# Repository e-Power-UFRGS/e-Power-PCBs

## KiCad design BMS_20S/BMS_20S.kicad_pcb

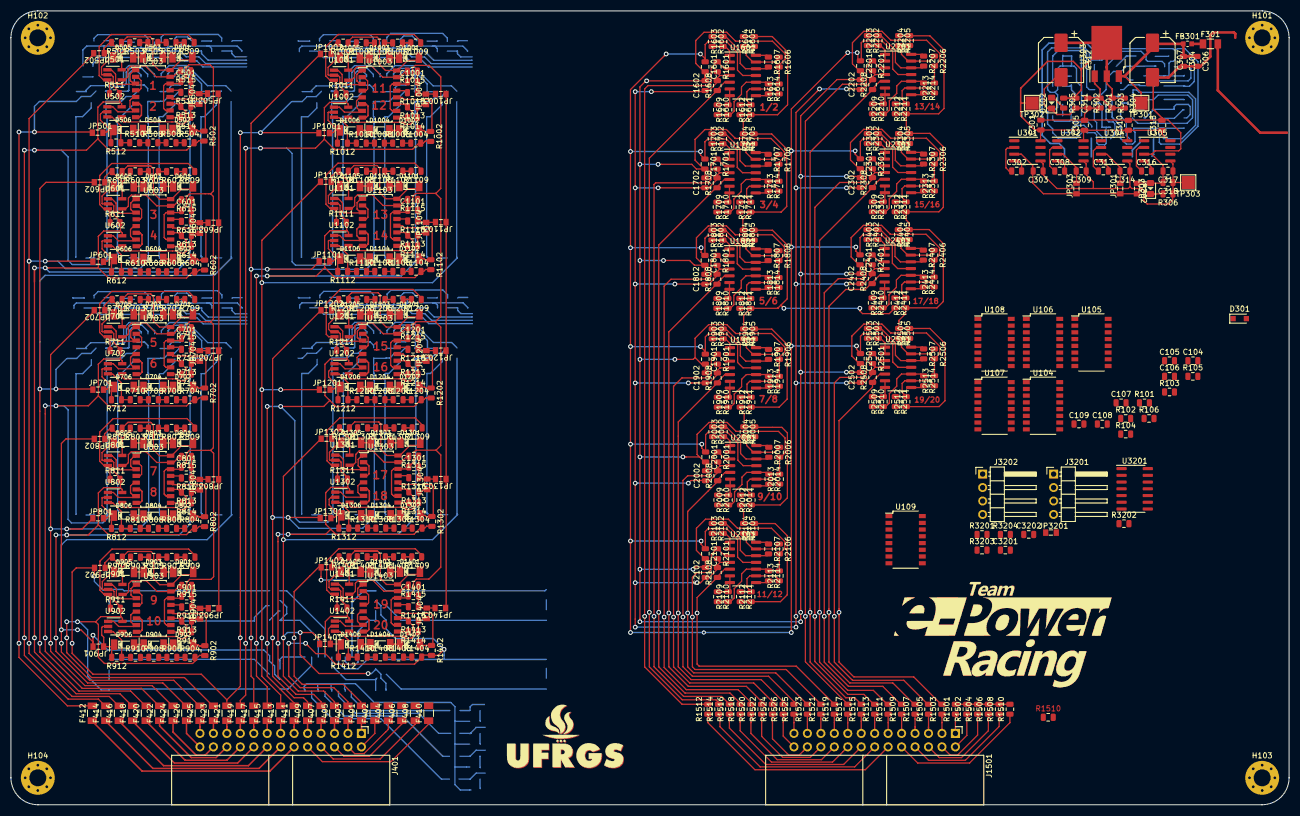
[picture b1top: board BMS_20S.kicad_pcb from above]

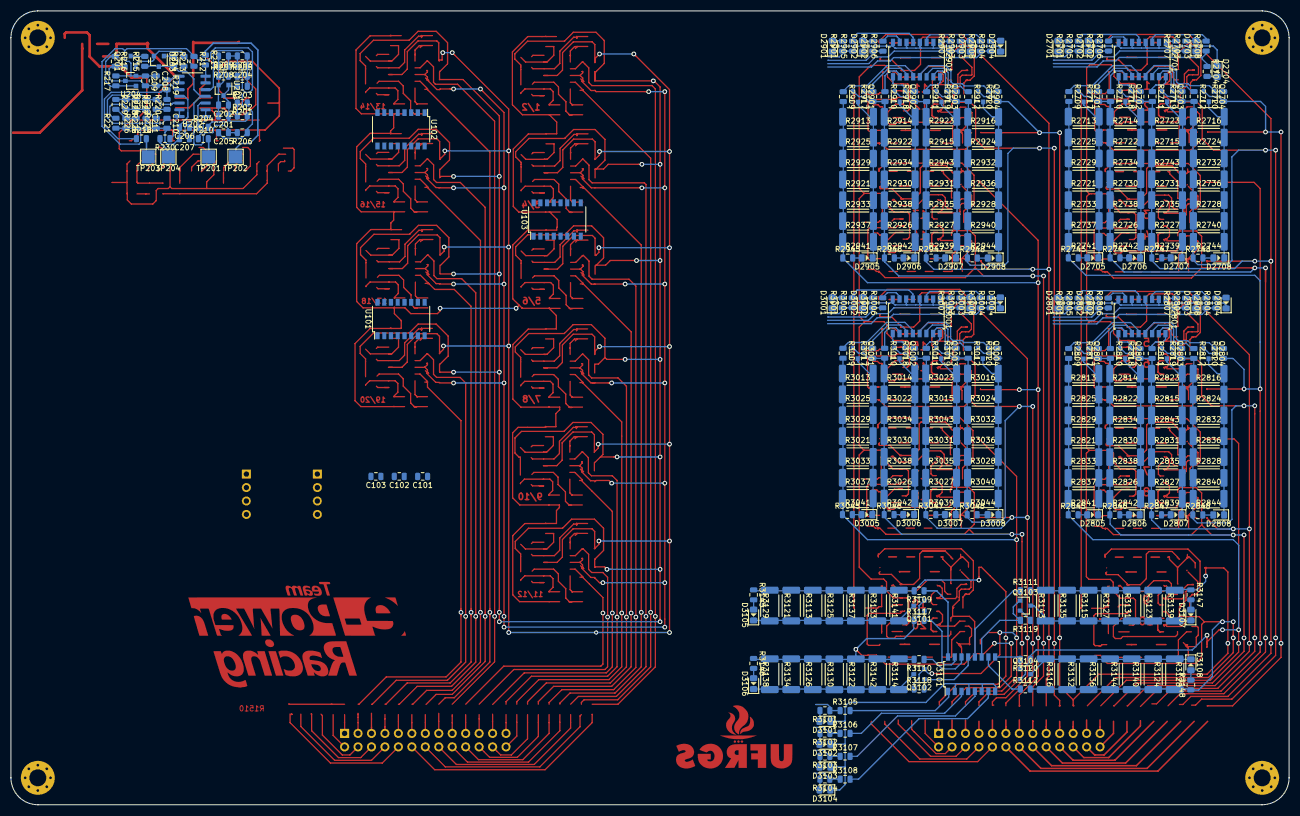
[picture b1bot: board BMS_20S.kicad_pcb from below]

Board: 4 copper layers, 241.3 x 149.9 mm, 958 parts (361 on the bottom side), 596 nets.

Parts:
C101, C102, C103, C104, C105, C106, C107, C108, C109, C202, C203, C205, C207, C209, C210, C301, C303, C304, C305, C309, C310, C311, C314, C315, C317, C501, C601, C701, C801, C901, C1001, C1101, C1201, C1301, C1401, C1601, C1602, C1701, C1702, C1801, C1802, C1901, C1902, C2001, C2002, C2101, C2102, C2201, C2202, C2301, C2302, C2401, C2402, C2501, C2502, C3201, C3202: 100nF; C_0805_2012Metric
C201, C204, C206, C208, C211, C302, C306, C308, C313, C316, C318: 10uF; C_0805_2012Metric
C307, C312: 470uF; CP_Elec_8x10
D301: 1N5819; D_SOD-323_HandSoldering
D302, D303, D2701, D2702, D2703, D2704, D2705, D2706, D2707, D2708, D2801, D2802, D2803, D2804, D2805, D2806, D2807, D2808, D2901, D2902, D2903, D2904, D2905, D2906, D2907, D2908, D3001, D3002, D3003, D3004, D3005, D3006, D3007, D3008, D3101, D3102, D3103, D3104, D3105, D3106, D3107, D3108: LED; LED_0805_1.15x1.40mm_HandSolder
D501, D502, D503, D504, D505, D506, D601, D602, D603, D604, D605, D606, D701, D702, D703, D704, D705, D706, D801, D802, D803, D804, D805, D806, D901, D902, D903, D904, D905, D906, D1001, D1002, D1003, D1004, D1005, D1006, D1101, D1102, D1103, D1104, D1105, D1106, D1201, D1202, D1203, D1204, D1205, D1206, D1301, D1302, D1303, D1304, D1305, D1306, D1401, D1402, D1403, D1404, D1405, D1406: LL4148; SOD-80
F301: Fuse_1206; FUSE_1206_3216Metric
F401, F402, F403, F404, F405, F406, F407, F408, F409, F410, F411, F412, F413, F414, F415, F416, F417, F418, F419, F420, F421, F422, F423, F424, F425, F426: Fuse; FUSE_1206_3216Metric
FB301: Ferrite_Bead; FB_0603_1608Metric
H101, H102, H103, H104: MountingHole_Pad; MountingHole_3.2mm_M3_Pad_Via
J401: VOLT_IDC_26_CONN; IDC-Header_2x13_P2.54mm_Horizontal
J1501: TEMP_IDC_26_CONN; IDC-Header_2x13_P2.54mm_Horizontal
J3201: Current_Conn; PinHeader_1x04_P2.54mm_Horizontal
J3202: BSPD_Conn; PinHeader_1x04_P2.54mm_Horizontal
JP301, JP302, JP303, JP501, JP502, JP503, JP504, JP601, JP602, JP603, JP604, JP701, JP702, JP703, JP704, JP801, JP802, JP803, JP804, JP901, JP902, JP903, JP904, JP1001, JP1002, JP1003, JP1004, JP1101, JP1102, JP1103, JP1104, JP1201, JP1202, JP1203, JP1204, JP1301, JP1302, JP1303, JP1304, JP1401, JP1402, JP1403, JP1404: 0R; zero_ohm_resistor_0805
JP3201: jumper; zero_ohm_resistor_0805
Q201: BC558; SOT-23
Q2701, Q2702, Q2703, Q2704, Q2801, Q2802, Q2803, Q2804, Q2901, Q2902, Q2903, Q2904, Q3001, Q3002, Q3003, Q3004, Q3101, Q3102, Q3103, Q3104: Si2302DS; SOT-23
R101, R102, R103, R104, R105, R106, R203, R204, R205, R207, R208, R209, R212, R213, R214, R215, R216, R217, R222, R223, R225, R228, R301, R501, R502, R503, R504, R505, R506, R507, R508, R509, R510, R511, R512, R513, R514, R515, R516, R601, R602, R603, R604, R605, R606, R607, R608, R609, R610, R611, R612, R613, R614, R615, R616, R701, R702, R703, R704, R705, R706, R707, R708, R709, R710, R711, R712, R713, R714, R715, R716, R801, R802, R803, R804, R805, R806, R807, R808, R809, R810, R811, R812, R813, R814, R815, R816, R901, R902, R903, R904, R905, R906, R907, R908, R909, R910, R911, R912, R913, R914, R915, R916, R1001, R1002, R1003, R1004, R1005, R1006, R1007, R1008, R1009, R1010, R1011, R1012, R1013, R1014, R1015, R1016, R1101, R1102, R1103, R1104, R1105, R1106, R1107, R1108, R1109, R1110, R1111, R1112, R1113, R1114, R1115, R1116, R1201, R1202, R1203, R1204, R1205, R1206, R1207, R1208, R1209, R1210, R1211, R1212, R1213, R1214, R1215, R1216, R1301, R1302, R1303, R1304, R1305, R1306, R1307, R1308, R1309, R1310, R1311, R1312, R1313, R1314, R1315, R1316, R1401, R1402, R1403, R1404, R1405, R1406, R1407, R1408, R1409, R1410, R1411, R1412, R1413, R1414, R1415, R1416, R1601, R1608, R1701, R1708, R1801, R1808, R1901, R1908, R2001, R2008, R2101, R2108, R2201, R2208, R2301, R2308, R2401, R2408, R2501, R2508, R2709, R2710, R2711, R2712, R2809, R2810, R2811, R2812, R2909, R2910, R2911, R2912, R3009, R3010, R3011, R3012, R3109, R3110, R3111, R3112: 1K; R_0805_2012Metric
R201, R202: 100R; R_0805_2012Metric
R206, R220, R1602, R1603, R1604, R1605, R1606, R1607, R1609, R1610, R1611, R1612, R1613, R1614, R1702, R1703, R1704, R1705, R1706, R1707, R1709, R1710, R1711, R1712, R1713, R1714, R1802, R1803, R1804, R1805, R1806, R1807, R1809, R1810, R1811, R1812, R1813, R1814, R1902, R1903, R1904, R1905, R1906, R1907, R1909, R1910, R1911, R1912, R1913, R1914, R2002, R2003, R2004, R2005, R2006, R2007, R2009, R2010, R2011, R2012, R2013, R2014, R2102, R2103, R2104, R2105, R2106, R2107, R2109, R2110, R2111, R2112, R2113, R2114, R2202, R2203, R2204, R2205, R2206, R2207, R2209, R2210, R2211, R2212, R2213, R2214, R2302, R2303, R2304, R2305, R2306, R2307, R2309, R2310, R2311, R2312, R2313, R2314, R2402, R2403, R2404, R2405, R2406, R2407, R2409, R2410, R2411, R2412, R2413, R2414, R2502, R2503, R2504, R2505, R2506, R2507, R2509, R2510, R2511, R2512, R2513, R2514, R2717, R2718, R2719, R2720, R2817, R2818, R2819, R2820, R2917, R2918, R2919, R2920, R3017, R3018, R3019, R3020, R3117, R3118, R3119, R3120, R3201, R3202, R3203, R3204: 10K; R_0805_2012Metric
R210, R211, R218, R219, R224, R229, R230, R1501, R1502, R1503, R1504, R1505, R1506, R1507, R1508, R1509, R1510, R1510#2, R1511, R1512, R1513, R1514, R1515, R1516, R1517, R1518, R1519, R1520, R1521, R1522, R1523, R1524, R1525, R1526: 0R; R_0805_2012Metric
R221, R226, R227: 100K; R_0805_2012Metric
R302, R304: ADJ; R_0805_2012Metric
R303, R305, R306, R2701, R2702, R2703, R2704, R2705, R2706, R2707, R2708, R2745, R2746, R2747, R2748, R2801, R2802, R2803, R2804, R2805, R2806, R2807, R2808, R2845, R2846, R2847, R2848, R2901, R2902, R2903, R2904, R2905, R2906, R2907, R2908, R2945, R2946, R2947, R2948, R3001, R3002, R3003, R3004, R3005, R3006, R3007, R3008, R3045, R3046, R3047, R3048, R3101, R3102, R3103, R3104, R3105, R3106, R3107, R3108, R3145, R3146, R3147, R3148: 330R; R_0805_2012Metric
R2713, R2714, R2715, R2716, R2721, R2722, R2723, R2724, R2725, R2726, R2727, R2728, R2729, R2730, R2731, R2732, R2733, R2734, R2735, R2736, R2737, R2738, R2739, R2740, R2741, R2742, R2743, R2744, R2813, R2814, R2815, R2816, R2821, R2822, R2823, R2824, R2825, R2826, R2827, R2828, R2829, R2830, R2831, R2832, R2833, R2834, R2835, R2836, R2837, R2838, R2839, R2840, R2841, R2842, R2843, R2844, R2913, R2914, R2915, R2916, R2921, R2922, R2923, R2924, R2925, R2926, R2927, R2928, R2929, R2930, R2931, R2932, R2933, R2934, R2935, R2936, R2937, R2938, R2939, R2940, R2941, R2942, R2943, R2944, R3013, R3014, R3015, R3016, R3021, R3022, R3023, R3024, R3025, R3026, R3027, R3028, R3029, R3030, R3031, R3032, R3033, R3034, R3035, R3036, R3037, R3038, R3039, R3040, R3041, R3042, R3043, R3044, R3113, R3114, R3115, R3116, R3121, R3122, R3123, R3124, R3125, R3126, R3127, R3128, R3129, R3130, R3131, R3132, R3133, R3134, R3135, R3136, R3137, R3138, R3139, R3140, R3141, R3142, R3143, R3144: 100R; R_2512_6332Metric
TP201: 2.2727V_TP; TestPoint_Pad_2.5x2.5mm
TP202: 1.8V_TP; TestPoint_Pad_2.5x2.5mm
TP203: 5.000V_TP; TestPoint_Pad_2.5x2.5mm
TP204: 0.850V_TP; TestPoint_Pad_2.5x2.5mm
TP301: 12V_TP; TestPoint_Pad_2.5x2.5mm
TP302: 5V_TP; TestPoint_Pad_2.5x2.5mm
TP303: -5V_TP; TestPoint_Pad_2.5x2.5mm
U101, U102, U103, U104, U105, U106: 74HC4051; SOP-16_4.4x10.4mm_P1.27mm
U107, U108, U109: 74HC595; SOP-16_4.4x10.4mm_P1.27mm
U201, U203, U204: TL431LP; SOT-23
U202, U1601, U1701, U1801, U1901, U2001, U2101, U2201, U2301, U2401, U2501, U3201: LM324; SOIC-14_3.9x8.7mm_P1.27mm
U301, U302, U304, U305: LMC7660; SOIC-8_3.9x4.9mm_P1.27mm
U303: LM317_3PinPackage; TO-252-3_TabPin2
U501, U502, U601, U602, U701, U702, U801, U802, U901, U902, U1001, U1002, U1101, U1102, U1201, U1202, U1301, U1302, U1401, U1402: TS1851ILT; SOT-23-5_HandSoldering
U503, U603, U703, U803, U903, U1003, U1103, U1203, U1303, U1403, U2701, U2801, U2901, U3001, U3101: TLP290-4; SOIC-16_4.55x10.3mm_P1.27mm(TLP290-4)

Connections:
+5V: C101.2, C102.2, C103.2, C104.2, C105.2, C106.2, C107.2, C108.2, C109.2, C301.1, C303.1, C305.1, C309.1, C310.1, C311.1, C312.1, C314.1, C315.1, C317.1, C318.1, C1601.1, C1602.1, C1701.1, C1702.1, C1801.1, C1802.1, C1901.1, C1902.1, C2001.1, C2002.1, C2101.1, C2102.1, C2201.1, C2202.1, C2301.1, C2302.1, C2401.1, C2402.1, C2501.1, C2502.1, C3201.1, C3202.1, R201.1, R303.1, R304.1, R305.1, R306.1, R1601.2, R1608.2, R1701.2, R1708.2, R1801.2, R1808.2, R1901.2, R1908.2, R2001.2, R2008.2, R2101.2, R2108.2, R2201.2, R2208.2, R2301.2, R2308.2, R2401.2, R2408.2, R2501.2, R2508.2, TP302.1, TP303.1, U101.16, U102.16, U103.16, U104.16, U105.16, U106.16, U107.16, U108.16, U109.16, U301.5, U301.8, U302.5, U302.8, U303.2, U304.5, U304.8, U305.5, U305.8, U1601.4, U1601.11, U1701.4, U1701.11, U1801.4, U1801.11, U1901.4, U1901.11, U2001.4, U2001.11, U2101.4, U2101.11, U2201.4, U2201.11, U2301.4, U2301.11, U2401.4, U2401.11, U2501.4, U2501.11, U3201.4, U3201.11
+12V: C207.1, C304.1, C306.1, C307.1, FB301.1, R213.2, R215.1, TP301.1, U202.4, U203.3, U303.3
/0.850V: R230.2, R3202.2, TP204.1
/1.8V: C501.1, C601.1, C701.1, C801.1, C901.1, C1001.1, C1101.1, C1201.1, C1301.1, C1401.1, R211.1, TP202.1, U503.10, U503.14, U603.10, U603.14, U703.10, U703.14, U803.10, U803.14, U903.10, U903.14, U1003.10, U1003.14, U1103.10, U1103.14, U1203.10, U1203.14, U1303.10, U1303.14, U1403.10, U1403.14
/2.2727V: R210.2, R1604.2, R1605.1, R1611.2, R1612.1, R1704.2, R1705.1, R1711.2, R1712.1, R1804.2, R1805.1, R1811.2, R1812.1, R1904.2, R1905.1, R1911.2, R1912.1, R2004.2, R2005.1, R2011.2, R2012.1, R2104.2, R2105.1, R2111.2, R2112.1, R2204.2, R2205.1, R2211.2, R2212.1, R2304.2, R2305.1, R2311.2, R2312.1, R2404.2, R2405.1, R2411.2, R2412.1, R2504.2, R2505.1, R2511.2, R2512.1, TP201.1
/5.000V: JP3201.1, R218.2, TP203.1
/B1: R2704.1, R2708.1, U107.15
/B2: R2703.1, R2707.1, U107.1
/B3: R2702.1, R2706.1, U107.2
/B4: R2701.1, R2705.1, U107.3
/B5: R2804.1, R2808.1, U107.4
/B6: R2803.1, R2807.1, U107.5
/B7: R2802.1, R2806.1, U107.6
/B8: R2801.1, R2805.1, U107.7
/B9: R3104.1, R3108.1, U108.15
/B10: R3103.1, R3107.1, U108.1
/B11: R2904.1, R2908.1, U108.2
/B12: R2903.1, R2907.1, U108.3
/B13: R2902.1, R2906.1, U108.4
/B14: R2901.1, R2905.1, U108.5
/B15: R3004.1, R3008.1, U108.6
/B16: R3003.1, R3007.1, U108.7
/Balancing/B17: R3002.1, R3006.1
/Balancing/B18: R3001.1, R3005.1
/Balancing/B19: R3102.1, R3106.1
/Balancing/B20: R3101.1, R3105.1
/C1: R3204.2, U3201.8
/Current Sensor/BSPD_SIG: J3202.1, U3201.6, U3201.7
/Current Sensor/VIOUT: J3201.3, U3201.3, U3201.5
/RCLK: U107.12, U108.12, U109.12
/S0: U101.11, U102.11, U103.11, U104.11, U105.11, U106.11
/S1: U101.10, U102.10, U103.10, U104.10, U105.10, U106.10
/S2: U101.9, U102.9, U103.9, U104.9, U105.9, U106.9
/SCLK: U107.11, U108.11, U109.11
/T1: R1607.1, U103.13, U1601.14
/T2: R1614.2, U103.14, U1601.8
/T3: R1707.1, U103.15, U1701.14
/T4: R1714.2, U103.12, U1701.8
/T5: R1807.1, U103.1, U1801.14
/T6: R1814.2, U103.5, U1801.8
/T7: R1907.1, U103.2, U1901.14
/T8: R1914.2, U103.4, U1901.8
/T9: R2007.1, U102.13, U2001.14
/T10: R2014.2, U102.14, U2001.8
/T11: R2107.1, U102.15, U2101.14
/T12: R2114.2, U102.12, U2101.8
/T13: R2207.1, U102.1, U2201.14
/T14: R2214.2, U102.5, U2201.8
/T15: R2307.1, U102.2, U2301.14
/T16: R2314.2, U102.4, U2301.8
/T17: R2407.1, U101.13, U2401.14
/T18: R2414.2, U101.14, U2401.8
/T19: R2507.1, U101.15, U2501.14
/T20: R2514.2, U101.12, U2501.8
/Temperature Sensors/0V: R1501.2, R1502.2, R1504.2, R1506.2, R1508.2, R1510.2, R1510#2.2
/Temperature Sensors/TS_1: R1512.2, R1601.1, U1601.3
/Temperature Sensors/TS_2: R1514.2, R1608.1, U1601.5
/Temperature Sensors/TS_3: R1516.2, R1701.1, U1701.3
/Temperature Sensors/TS_4: R1518.2, R1708.1, U1701.5
/Temperature Sensors/TS_5: R1520.2, R1801.1, U1801.3
/Temperature Sensors/TS_6: R1522.2, R1808.1, U1801.5
/Temperature Sensors/TS_7: R1524.2, R1901.1, U1901.3
/Temperature Sensors/TS_8: R1526.2, R1908.1, U1901.5
/Temperature Sensors/TS_9: R1525.2, R2001.1, U2001.3
/Temperature Sensors/TS_10: R1523.2, R2008.1, U2001.5
/Temperature Sensors/TS_11: R1521.2, R2101.1, U2101.3
/Temperature Sensors/TS_12: R1519.2, R2108.1, U2101.5
/Temperature Sensors/TS_13: R1517.2, R2201.1, U2201.3
/Temperature Sensors/TS_14: R1515.2, R2208.1, U2201.5
/Temperature Sensors/TS_15: R1513.2, R2301.1, U2301.3
/Temperature Sensors/TS_16: R1511.2, R2308.1, U2301.5
/Temperature Sensors/TS_17: R1509.2, R2401.1, U2401.3
/Temperature Sensors/TS_18: R1507.2, R2408.1, U2401.5
/Temperature Sensors/TS_19: R1505.2, R2501.1, U2501.3
/Temperature Sensors/TS_20: R1503.2, R2508.1, U2501.5
/V1: R514.2, U106.13, U503.9
/V2: R516.2, U106.14, U503.13
/V3: R614.2, U106.15, U603.9
/V4: R616.2, U106.12, U603.13
/V5: R714.2, U106.1, U703.9
/V6: R716.2, U106.5, U703.13
/V7: R814.2, U106.2, U803.9
/V8: R816.2, U106.4, U803.13
/V9: R914.2, U105.13, U903.9
/V10: R916.2, U105.14, U903.13
/V11: R1014.2, U105.15, U1003.9
/V12: R1016.2, U105.12, U1003.13
/V13: R1114.2, U105.1, U1103.9
/V14: R1116.2, U105.5, U1103.13
/V15: R1214.2, U105.2, U1203.9
/V16: R1216.2, U105.4, U1203.13
/Voltage Sensors/V17: R1314.2, U1303.9
/Voltage Sensors/V18: R1316.2, U1303.13
/Voltage Sensors/V19: R1414.2, U1403.9
/Voltage Sensors/V20: R1416.2, U1403.13
/~OE: U107.13, U108.13, U109.13
/~RESET: U107.10, U108.10, U109.10
CELL_1: D505.1, F414.2, Q2703.2, R502.2, R504.2, R511.2, R2712.2, R2716.2, R2719.1, R2724.2, R2728.2, R2732.2, R2736.2, R2740.2, R2744.2, R2748.1, U501.2, U502.5
CELL_2: D606.1, F416.2, JP502.1, JP601.1, Q2702.2, R501.2, R503.2, R612.2, R2711.2, R2715.2, R2718.1, R2723.2, R2727.2, R2731.2, R2735.2, R2739.2, R2743.2, R2747.1, U501.5, U602.2
CELL_3: D605.1, F418.2, Q2701.2, R602.2, R604.2, R611.2, R2710.2, R2714.2, R2717.1, R2722.2, R2726.2, R2730.2, R2734.2, R2738.2, R2742.2, R2746.1, U601.2, U602.5
CELL_4: D706.1, F420.2, JP602.1, JP701.1, Q2804.2, R601.2, R603.2, R712.2, R2709.2, R2713.2, R2721.2, R2725.2, R2729.2, R2733.2, R2737.2, R2741.2, R2745.1, R2820.1, U601.5, U702.2
CELL_5: D705.1, F422.2, Q2803.2, R702.2, R704.2, R711.2, R2812.2, R2816.2, R2819.1, R2824.2, R2828.2, R2832.2, R2836.2, R2840.2, R2844.2, R2848.1, U701.2, U702.5
CELL_6: D806.1, F424.2, JP702.1, JP801.1, Q2802.2, R701.2, R703.2, R812.2, R2811.2, R2815.2, R2818.1, R2823.2, R2827.2, R2831.2, R2835.2, R2839.2, R2843.2, R2847.1, U701.5, U802.2
CELL_7: D805.1, F426.2, Q2801.2, R802.2, R804.2, R811.2, R2810.2, R2814.2, R2817.1, R2822.2, R2826.2, R2830.2, R2834.2, R2838.2, R2842.2, R2846.1, U801.2, U802.5
CELL_8: D906.1, F425.2, JP802.1, JP901.1, Q3104.2, R801.2, R803.2, R912.2, R2809.2, R2813.2, R2821.2, R2825.2, R2829.2, R2833.2, R2837.2, R2841.2, R2845.1, R3120.1, U801.5, U902.2
CELL_9: D905.1, F423.2, Q3103.2, R902.2, R904.2, R911.2, R3112.2, R3116.2, R3119.1, R3124.2, R3128.2, R3132.2, R3136.2, R3140.2, R3144.2, R3148.1, U901.2, U902.5
CELL_10: D1006.1, F421.2, JP902.1, JP1001.1, Q2904.2, R901.2, R903.2, R1012.2, R2920.1, R3111.2, R3115.2, R3123.2, R3127.2, R3131.2, R3135.2, R3139.2, R3143.2, R3147.1, U901.5, U1002.2
CELL_11: D1005.1, F419.2, Q2903.2, R1002.2, R1004.2, R1011.2, R2912.2, R2916.2, R2919.1, R2924.2, R2928.2, R2932.2, R2936.2, R2940.2, R2944.2, R2948.1, U1001.2, U1002.5
CELL_12: D1106.1, F417.2, JP1002.1, JP1101.1, Q2902.2, R1001.2, R1003.2, R1112.2, R2911.2, R2915.2, R2918.1, R2923.2, R2927.2, R2931.2, R2935.2, R2939.2, R2943.2, R2947.1, U1001.5, U1102.2
CELL_13: D1105.1, F408.2, F410.2, F415.2, Q2901.2, R1102.2, R1104.2, R1111.2, R2910.2, R2914.2, R2917.1, R2922.2, R2926.2, R2930.2, R2934.2, R2938.2, R2942.2, R2946.1, U1101.2, U1102.5
CELL_14: D1206.1, F413.2, JP1102.1, JP1201.1, Q3004.2, R1101.2, R1103.2, R1212.2, R2909.2, R2913.2, R2921.2, R2925.2, R2929.2, R2933.2, R2937.2, R2941.2, R2945.1, R3020.1, U1101.5, U1202.2
CELL_15: D1205.1, F411.2, Q3003.2, R1202.2, R1204.2, R1211.2, R3012.2, R3016.2, R3019.1, R3024.2, R3028.2, R3032.2, R3036.2, R3040.2, R3044.2, R3048.1, U1201.2, U1202.5
CELL_16: D1306.1, F409.2, JP1202.1, JP1301.1, Q3002.2, R1201.2, R1203.2, R1312.2, R3011.2, R3015.2, R3018.1, R3023.2, R3027.2, R3031.2, R3035.2, R3039.2, R3043.2, R3047.1, U1201.5, U1302.2
CELL_17: D1305.1, F407.2, Q3001.2, R1302.2, R1304.2, R1311.2, R3010.2, R3014.2, R3017.1, R3022.2, R3026.2, R3030.2, R3034.2, R3038.2, R3042.2, R3046.1, U1301.2, U1302.5
CELL_18: D1406.1, F405.2, JP1302.1, JP1401.1, Q3102.2, R1301.2, R1303.2, R1412.2, R3009.2, R3013.2, R3021.2, R3025.2, R3029.2, R3033.2, R3037.2, R3041.2, R3045.1, R3118.1, U1301.5, U1402.2
CELL_19: D1405.1, F403.2, Q3101.2, R1402.2, R1404.2, R1411.2, R3110.2, R3114.2, R3117.1, R3122.2, R3126.2, R3130.2, R3134.2, R3138.2, R3142.2, R3146.1, U1401.2, U1402.5
CELL_20: F401.2, JP1402.1, R1401.2, R1403.2, R3109.2, R3113.2, R3121.2, R3125.2, R3129.2, R3133.2, R3137.2, R3141.2, R3145.1, U1401.5
CELL_GND: D506.1, F412.2, JP501.1, Q2704.2, R512.2, R2720.1, U502.2
GND: C101.1, C102.1, C103.1, C104.1, C105.1, C106.1, C107.1, C108.1, C109.1, C201.2, C202.2, C203.2, C204.2, C205.2, C206.2, C207.2, C208.1, C209.1, C210.2, C211.2, C301.2, C303.2, C304.2, C305.2, C306.2, C307.2, C309.2, C310.2, C311.2, C312.2, C314.2, C315.2, C317.2, C318.2, C501.2, C601.2, C701.2, C801.2, C901.2, C1001.2, C1101.2, C1201.2, C1301.2, C1401.2, C1601.2, C1602.2, C1701.2, C1702.2, C1801.2, C1802.2, C1901.2, C1902.2, C2001.2, C2002.2, C2101.2, C2102.2, C2201.2, C2202.2, C2301.2, C2302.2, C2401.2, C2402.2, C2501.2, C2502.2, C3201.2, C3202.2, D302.1, D303.2, D2701.1, D2702.1, D2703.1, D2704.1, D2801.1, D2802.1, D2803.1, D2804.1, D2901.1, D2902.1, D2903.1, D2904.1, D3001.1, D3002.1, D3003.1, D3004.1, D3101.1, D3102.1, D3103.1, D3104.1, H101.1, H102.1, H103.1, H104.1, J3201.2, J3202.2, JP301.1, JP302.1, JP303.1, JP503.1, JP504.1, JP603.1, JP604.1, JP703.1, JP704.1, JP803.1, JP804.1, JP903.1, JP904.1, JP1003.1, JP1004.1, JP1103.1, JP1104.1, JP1203.1, JP1204.1, JP1303.1, JP1304.1, JP1403.1, JP1404.1, R101.1, R102.1, R103.1, R104.1, R105.1, R106.1, R206.1, R208.1, R209.1, R212.1, R217.2, R221.1, R223.1, R225.2, R226.1, R301.2, R302.2, R513.1, R514.1, R515.1, R516.1, R613.1, R614.1, R615.1, R616.1, R713.1, R714.1, R715.1, R716.1, R813.1, R814.1, R815.1, R816.1, R913.1, R914.1, R915.1, R916.1, R1013.1, R1014.1, R1015.1, R1016.1, R1113.1, R1114.1, R1115.1, R1116.1, R1213.1, R1214.1, R1215.1, R1216.1, R1313.1, R1314.1, R1315.1, R1316.1, R1413.1, R1414.1, R1415.1, R1416.1, R1606.2, R1613.2, R1706.2, R1713.2, R1806.2, R1813.2, R1906.2, R1913.2, R2006.2, R2013.2, R2106.2, R2113.2, R2206.2, R2213.2, R2306.2, R2313.2, R2406.2, R2413.2, R2506.2, R2513.2, R3203.1, U101.7, U101.8, U102.7, U102.8, U103.7, U103.8, U104.7, U104.8, U105.7, U105.8, U106.7, U106.8, U107.8, U108.8, U109.8, U201.2, U202.11, U204.2, U301.3, U302.3, U304.3, U305.3, U2701.2, U2701.4, U2701.6, U2701.8, U2801.2, U2801.4, U2801.6, U2801.8, U2901.2, U2901.4, U2901.6, U2901.8, U3001.2, U3001.4, U3001.6, U3001.8, U3101.2, U3101.4, U3101.6, U3101.8
unnamed: C201.1, C202.1, R202.2, R203.2, R204.2, U201.1, U201.3
unnamed: C203.1, C204.1, R203.1, R205.2, U202.5
unnamed: C205.1, C206.1, R204.1, R206.2, U202.3
unnamed: C208.2, C209.2, Q201.1, R216.2, U202.10, U204.3
unnamed: C210.1, C211.1, R222.2, R224.2, U202.12
unnamed: C302.1, U301.2
unnamed: C302.2, U301.4
unnamed: C308.1, U302.2
unnamed: C308.2, U302.4
unnamed: C313.1, U304.2
unnamed: C313.2, U304.4
unnamed: C316.1, U305.2
unnamed: C316.2, U305.4
unnamed: D301.1, FB301.2
unnamed: D301.2, F301.1
unnamed: D302.2, R305.2
unnamed: D303.1, R306.2
unnamed: D501.1, D503.2
unnamed: D501.2, R501.1, U503.16
unnamed: D502.1, D504.2
unnamed: D502.2, R502.1, U503.12
unnamed: D503.1, D505.2
unnamed: D504.1, D506.2
unnamed: D601.1, D603.2
unnamed: D601.2, R601.1, U603.16
unnamed: D602.1, D604.2
unnamed: D602.2, R602.1, U603.12
unnamed: D603.1, D605.2
unnamed: D604.1, D606.2
unnamed: D701.1, D703.2
unnamed: D701.2, R701.1, U703.16
unnamed: D702.1, D704.2
unnamed: D702.2, R702.1, U703.12
unnamed: D703.1, D705.2
unnamed: D704.1, D706.2
unnamed: D801.1, D803.2
unnamed: D801.2, R801.1, U803.16
unnamed: D802.1, D804.2
unnamed: D802.2, R802.1, U803.12
unnamed: D803.1, D805.2
unnamed: D804.1, D806.2
unnamed: D901.1, D903.2
unnamed: D901.2, R901.1, U903.16
unnamed: D902.1, D904.2
unnamed: D902.2, R902.1, U903.12
unnamed: D903.1, D905.2
unnamed: D904.1, D906.2
unnamed: D1001.1, D1003.2
unnamed: D1001.2, R1001.1, U1003.16
unnamed: D1002.1, D1004.2
unnamed: D1002.2, R1002.1, U1003.12
unnamed: D1003.1, D1005.2
unnamed: D1004.1, D1006.2
unnamed: D1101.1, D1103.2
unnamed: D1101.2, R1101.1, U1103.16
unnamed: D1102.1, D1104.2
unnamed: D1102.2, R1102.1, U1103.12
unnamed: D1103.1, D1105.2
unnamed: D1104.1, D1106.2
unnamed: D1201.1, D1203.2
unnamed: D1201.2, R1201.1, U1203.16
unnamed: D1202.1, D1204.2
unnamed: D1202.2, R1202.1, U1203.12
unnamed: D1203.1, D1205.2
unnamed: D1204.1, D1206.2
unnamed: D1301.1, D1303.2
unnamed: D1301.2, R1301.1, U1303.16
unnamed: D1302.1, D1304.2
unnamed: D1302.2, R1302.1, U1303.12
unnamed: D1303.1, D1305.2
unnamed: D1304.1, D1306.2
unnamed: D1401.1, D1403.2
unnamed: D1401.2, R1401.1, U1403.16
unnamed: D1402.1, D1404.2
unnamed: D1402.2, R1402.1, U1403.12
unnamed: D1403.1, D1405.2
unnamed: D1404.1, D1406.2
unnamed: D2701.2, R2701.2
unnamed: D2702.2, R2702.2
unnamed: D2703.2, R2703.2
unnamed: D2704.2, R2704.2
unnamed: D2705.1, Q2701.3, R2713.1, R2721.1, R2725.1, R2729.1, R2733.1, R2737.1, R2741.1
unnamed: D2705.2, R2745.2
unnamed: D2706.1, Q2702.3, R2714.1, R2722.1, R2726.1, R2730.1, R2734.1, R2738.1, R2742.1
unnamed: D2706.2, R2746.2
unnamed: D2707.1, Q2703.3, R2715.1, R2723.1, R2727.1, R2731.1, R2735.1, R2739.1, R2743.1
unnamed: D2707.2, R2747.2
unnamed: D2708.1, Q2704.3, R2716.1, R2724.1, R2728.1, R2732.1, R2736.1, R2740.1, R2744.1
unnamed: D2708.2, R2748.2
unnamed: D2801.2, R2801.2
unnamed: D2802.2, R2802.2
unnamed: D2803.2, R2803.2
unnamed: D2804.2, R2804.2
unnamed: D2805.1, Q2801.3, R2813.1, R2821.1, R2825.1, R2829.1, R2833.1, R2837.1, R2841.1
unnamed: D2805.2, R2845.2
unnamed: D2806.1, Q2802.3, R2814.1, R2822.1, R2826.1, R2830.1, R2834.1, R2838.1, R2842.1
unnamed: D2806.2, R2846.2
unnamed: D2807.1, Q2803.3, R2815.1, R2823.1, R2827.1, R2831.1, R2835.1, R2839.1, R2843.1
unnamed: D2807.2, R2847.2
unnamed: D2808.1, Q2804.3, R2816.1, R2824.1, R2828.1, R2832.1, R2836.1, R2840.1, R2844.1
unnamed: D2808.2, R2848.2
unnamed: D2901.2, R2901.2
unnamed: D2902.2, R2902.2
unnamed: D2903.2, R2903.2
unnamed: D2904.2, R2904.2
unnamed: D2905.1, Q2901.3, R2913.1, R2921.1, R2925.1, R2929.1, R2933.1, R2937.1, R2941.1
unnamed: D2905.2, R2945.2
unnamed: D2906.1, Q2902.3, R2914.1, R2922.1, R2926.1, R2930.1, R2934.1, R2938.1, R2942.1
unnamed: D2906.2, R2946.2
unnamed: D2907.1, Q2903.3, R2915.1, R2923.1, R2927.1, R2931.1, R2935.1, R2939.1, R2943.1
unnamed: D2907.2, R2947.2
unnamed: D2908.1, Q2904.3, R2916.1, R2924.1, R2928.1, R2932.1, R2936.1, R2940.1, R2944.1
unnamed: D2908.2, R2948.2
unnamed: D3001.2, R3001.2
unnamed: D3002.2, R3002.2
unnamed: D3003.2, R3003.2
unnamed: D3004.2, R3004.2
unnamed: D3005.1, Q3001.3, R3013.1, R3021.1, R3025.1, R3029.1, R3033.1, R3037.1, R3041.1
unnamed: D3005.2, R3045.2
unnamed: D3006.1, Q3002.3, R3014.1, R3022.1, R3026.1, R3030.1, R3034.1, R3038.1, R3042.1
unnamed: D3006.2, R3046.2
unnamed: D3007.1, Q3003.3, R3015.1, R3023.1, R3027.1, R3031.1, R3035.1, R3039.1, R3043.1
unnamed: D3007.2, R3047.2
unnamed: D3008.1, Q3004.3, R3016.1, R3024.1, R3028.1, R3032.1, R3036.1, R3040.1, R3044.1
unnamed: D3008.2, R3048.2
unnamed: D3101.2, R3101.2
unnamed: D3102.2, R3102.2
unnamed: D3103.2, R3103.2
unnamed: D3104.2, R3104.2
unnamed: D3105.1, Q3101.3, R3113.1, R3121.1, R3125.1, R3129.1, R3133.1, R3137.1, R3141.1
unnamed: D3105.2, R3145.2
unnamed: D3106.1, Q3102.3, R3114.1, R3122.1, R3126.1, R3130.1, R3134.1, R3138.1, R3142.1
unnamed: D3106.2, R3146.2
unnamed: D3107.1, Q3103.3, R3115.1, R3123.1, R3127.1, R3131.1, R3135.1, R3139.1, R3143.1
unnamed: D3107.2, R3147.2
unnamed: D3108.1, Q3104.3, R3116.1, R3124.1, R3128.1, R3132.1, R3136.1, R3140.1, R3144.1
unnamed: D3108.2, R3148.2
unnamed: F401.1, J401.1
unnamed: F402.1, J401.2
unnamed: F403.1, J401.3
unnamed: F404.1, J401.4
unnamed: F405.1, J401.5
unnamed: F406.1, J401.6
unnamed: F407.1, J401.7
unnamed: F408.1, J401.8
unnamed: F409.1, J401.9
unnamed: F410.1, J401.10
unnamed: F411.1, J401.11
unnamed: F412.1, J401.12
unnamed: F413.1, J401.13
unnamed: F414.1, J401.14
unnamed: F415.1, J401.15
unnamed: F416.1, J401.16
unnamed: F417.1, J401.17
unnamed: F418.1, J401.18
unnamed: F419.1, J401.19
unnamed: F420.1, J401.20
unnamed: F421.1, J401.21
unnamed: F422.1, J401.22
unnamed: F423.1, J401.23
unnamed: F424.1, J401.24
unnamed: F425.1, J401.25
unnamed: F426.1, J401.26
unnamed: J1501.1, R1501.1
unnamed: J1501.2, R1502.1
unnamed: J1501.3, R1503.1
unnamed: J1501.4, R1504.1
unnamed: J1501.5, R1505.1
unnamed: J1501.6, R1506.1
unnamed: J1501.7, R1507.1
unnamed: J1501.8, R1508.1
unnamed: J1501.9, R1509.1
unnamed: J1501.10, R1510.1, R1510#2.1
unnamed: J1501.11, R1511.1
unnamed: J1501.12, R1512.1
unnamed: J1501.13, R1513.1
unnamed: J1501.14, R1514.1
unnamed: J1501.15, R1515.1
unnamed: J1501.16, R1516.1
unnamed: J1501.17, R1517.1
unnamed: J1501.18, R1518.1
unnamed: J1501.19, R1519.1
unnamed: J1501.20, R1520.1
unnamed: J1501.21, R1521.1
unnamed: J1501.22, R1522.1
unnamed: J1501.23, R1523.1
unnamed: J1501.24, R1524.1
unnamed: J1501.25, R1525.1
unnamed: J1501.26, R1526.1
unnamed: Q201.2, R212.2, R214.2, U203.2
unnamed: Q201.3, R215.2
unnamed: Q2701.1, R2717.2, U2701.15
unnamed: Q2702.1, R2718.2, U2701.13
unnamed: Q2703.1, R2719.2, U2701.11
unnamed: Q2704.1, R2720.2, U2701.9
unnamed: Q2801.1, R2817.2, U2801.15
unnamed: Q2802.1, R2818.2, U2801.13
unnamed: Q2803.1, R2819.2, U2801.11
unnamed: Q2804.1, R2820.2, U2801.9
unnamed: Q2901.1, R2917.2, U2901.15
unnamed: Q2902.1, R2918.2, U2901.13
unnamed: Q2903.1, R2919.2, U2901.11
unnamed: Q2904.1, R2920.2, U2901.9
unnamed: Q3001.1, R3017.2, U3001.15
unnamed: Q3002.1, R3018.2, U3001.13
unnamed: Q3003.1, R3019.2, U3001.11
unnamed: Q3004.1, R3020.2, U3001.9
unnamed: Q3101.1, R3117.2, U3101.15
unnamed: Q3102.1, R3118.2, U3101.13
unnamed: Q3103.1, R3119.2, U3101.11
unnamed: Q3104.1, R3120.2, U3101.9
unnamed: R101.2, U101.6
unnamed: R102.2, U102.6
unnamed: R103.2, U103.6
unnamed: R104.2, U104.6
unnamed: R105.2, U105.6
unnamed: R106.2, U106.6
unnamed: R201.2, R202.1
unnamed: R205.1, R207.2
unnamed: R207.1, R208.2, R209.2
unnamed: R210.1, U202.1, U202.2
unnamed: R211.2, U202.6, U202.7
unnamed: R213.1, R214.1, U203.1
unnamed: R216.1, R217.1, U204.1
unnamed: R218.1, R219.2, R220.2
unnamed: R219.1, U202.8, U202.9
unnamed: R220.1, R222.1
unnamed: R221.2, R223.2, R224.1, R227.2, R228.2
unnamed: R225.1, R226.2, R229.2
unnamed: R227.1, R228.1, R229.1
unnamed: R230.1, U202.13, U202.14
unnamed: R301.1, R302.1, R303.2, R304.2, U303.1
unnamed: R503.1, R505.2
unnamed: R504.1, R506.2
unnamed: R505.1, R507.2
unnamed: R506.1, R508.2
unnamed: R507.1, R509.2
unnamed: R508.1, R510.2
unnamed: R509.1, R511.1, U501.3
unnamed: R510.1, R512.1, U502.3
unnamed: R513.2, U502.4, U503.11
unnamed: R515.2, U501.4, U503.15
unnamed: R603.1, R605.2
unnamed: R604.1, R606.2
unnamed: R605.1, R607.2
unnamed: R606.1, R608.2
unnamed: R607.1, R609.2
unnamed: R608.1, R610.2
unnamed: R609.1, R611.1, U601.3
unnamed: R610.1, R612.1, U602.3
unnamed: R613.2, U602.4, U603.11
unnamed: R615.2, U601.4, U603.15
unnamed: R703.1, R705.2
unnamed: R704.1, R706.2
unnamed: R705.1, R707.2
unnamed: R706.1, R708.2
unnamed: R707.1, R709.2
unnamed: R708.1, R710.2
unnamed: R709.1, R711.1, U701.3
unnamed: R710.1, R712.1, U702.3
unnamed: R713.2, U702.4, U703.11
unnamed: R715.2, U701.4, U703.15
unnamed: R803.1, R805.2
unnamed: R804.1, R806.2
unnamed: R805.1, R807.2
unnamed: R806.1, R808.2
unnamed: R807.1, R809.2
unnamed: R808.1, R810.2
unnamed: R809.1, R811.1, U801.3
unnamed: R810.1, R812.1, U802.3
unnamed: R813.2, U802.4, U803.11
unnamed: R815.2, U801.4, U803.15
unnamed: R903.1, R905.2
unnamed: R904.1, R906.2
unnamed: R905.1, R907.2
unnamed: R906.1, R908.2
unnamed: R907.1, R909.2
unnamed: R908.1, R910.2
unnamed: R909.1, R911.1, U901.3
unnamed: R910.1, R912.1, U902.3
unnamed: R913.2, U902.4, U903.11
unnamed: R915.2, U901.4, U903.15
unnamed: R1003.1, R1005.2
unnamed: R1004.1, R1006.2
unnamed: R1005.1, R1007.2
unnamed: R1006.1, R1008.2
unnamed: R1007.1, R1009.2
unnamed: R1008.1, R1010.2
unnamed: R1009.1, R1011.1, U1001.3
unnamed: R1010.1, R1012.1, U1002.3
unnamed: R1013.2, U1002.4, U1003.11
unnamed: R1015.2, U1001.4, U1003.15
unnamed: R1103.1, R1105.2
unnamed: R1104.1, R1106.2
unnamed: R1105.1, R1107.2
unnamed: R1106.1, R1108.2
unnamed: R1107.1, R1109.2
unnamed: R1108.1, R1110.2
unnamed: R1109.1, R1111.1, U1101.3
unnamed: R1110.1, R1112.1, U1102.3
unnamed: R1113.2, U1102.4, U1103.11
unnamed: R1115.2, U1101.4, U1103.15
unnamed: R1203.1, R1205.2
unnamed: R1204.1, R1206.2
unnamed: R1205.1, R1207.2
unnamed: R1206.1, R1208.2
unnamed: R1207.1, R1209.2
unnamed: R1208.1, R1210.2
unnamed: R1209.1, R1211.1, U1201.3
unnamed: R1210.1, R1212.1, U1202.3
unnamed: R1213.2, U1202.4, U1203.11
unnamed: R1215.2, U1201.4, U1203.15
unnamed: R1303.1, R1305.2
unnamed: R1304.1, R1306.2
unnamed: R1305.1, R1307.2
unnamed: R1306.1, R1308.2
unnamed: R1307.1, R1309.2
unnamed: R1308.1, R1310.2
unnamed: R1309.1, R1311.1, U1301.3
unnamed: R1310.1, R1312.1, U1302.3
unnamed: R1313.2, U1302.4, U1303.11
unnamed: R1315.2, U1301.4, U1303.15
unnamed: R1403.1, R1405.2
unnamed: R1404.1, R1406.2
unnamed: R1405.1, R1407.2
unnamed: R1406.1, R1408.2
unnamed: R1407.1, R1409.2
unnamed: R1408.1, R1410.2
unnamed: R1409.1, R1411.1, U1401.3
unnamed: R1410.1, R1412.1, U1402.3
unnamed: R1413.2, U1402.4, U1403.11
unnamed: R1415.2, U1401.4, U1403.15
unnamed: R1602.1, R1603.2, R1607.2, U1601.12
unnamed: R1602.2, R1603.1, U1601.1, U1601.2
unnamed: R1604.1, R1605.2, R1606.1, U1601.13
unnamed: R1609.1, R1610.2, R1614.1, U1601.10
unnamed: R1609.2, R1610.1, U1601.6, U1601.7
unnamed: R1611.1, R1612.2, R1613.1, U1601.9
unnamed: R1702.1, R1703.2, R1707.2, U1701.12
unnamed: R1702.2, R1703.1, U1701.1, U1701.2
unnamed: R1704.1, R1705.2, R1706.1, U1701.13
unnamed: R1709.1, R1710.2, R1714.1, U1701.10
unnamed: R1709.2, R1710.1, U1701.6, U1701.7
unnamed: R1711.1, R1712.2, R1713.1, U1701.9
unnamed: R1802.1, R1803.2, R1807.2, U1801.12
unnamed: R1802.2, R1803.1, U1801.1, U1801.2
unnamed: R1804.1, R1805.2, R1806.1, U1801.13
unnamed: R1809.1, R1810.2, R1814.1, U1801.10
unnamed: R1809.2, R1810.1, U1801.6, U1801.7
unnamed: R1811.1, R1812.2, R1813.1, U1801.9
unnamed: R1902.1, R1903.2, R1907.2, U1901.12
unnamed: R1902.2, R1903.1, U1901.1, U1901.2
unnamed: R1904.1, R1905.2, R1906.1, U1901.13
unnamed: R1909.1, R1910.2, R1914.1, U1901.10
unnamed: R1909.2, R1910.1, U1901.6, U1901.7
unnamed: R1911.1, R1912.2, R1913.1, U1901.9
unnamed: R2002.1, R2003.2, R2007.2, U2001.12
unnamed: R2002.2, R2003.1, U2001.1, U2001.2
unnamed: R2004.1, R2005.2, R2006.1, U2001.13
unnamed: R2009.1, R2010.2, R2014.1, U2001.10
unnamed: R2009.2, R2010.1, U2001.6, U2001.7
unnamed: R2011.1, R2012.2, R2013.1, U2001.9
unnamed: R2102.1, R2103.2, R2107.2, U2101.12
unnamed: R2102.2, R2103.1, U2101.1, U2101.2
unnamed: R2104.1, R2105.2, R2106.1, U2101.13
unnamed: R2109.1, R2110.2, R2114.1, U2101.10
unnamed: R2109.2, R2110.1, U2101.6, U2101.7
unnamed: R2111.1, R2112.2, R2113.1, U2101.9
unnamed: R2202.1, R2203.2, R2207.2, U2201.12
unnamed: R2202.2, R2203.1, U2201.1, U2201.2
unnamed: R2204.1, R2205.2, R2206.1, U2201.13
unnamed: R2209.1, R2210.2, R2214.1, U2201.10
unnamed: R2209.2, R2210.1, U2201.6, U2201.7
unnamed: R2211.1, R2212.2, R2213.1, U2201.9
unnamed: R2302.1, R2303.2, R2307.2, U2301.12
unnamed: R2302.2, R2303.1, U2301.1, U2301.2
unnamed: R2304.1, R2305.2, R2306.1, U2301.13
unnamed: R2309.1, R2310.2, R2314.1, U2301.10
unnamed: R2309.2, R2310.1, U2301.6, U2301.7
unnamed: R2311.1, R2312.2, R2313.1, U2301.9
unnamed: R2402.1, R2403.2, R2407.2, U2401.12
unnamed: R2402.2, R2403.1, U2401.1, U2401.2
unnamed: R2404.1, R2405.2, R2406.1, U2401.13
unnamed: R2409.1, R2410.2, R2414.1, U2401.10
unnamed: R2409.2, R2410.1, U2401.6, U2401.7
unnamed: R2411.1, R2412.2, R2413.1, U2401.9
unnamed: R2502.1, R2503.2, R2507.2, U2501.12
unnamed: R2502.2, R2503.1, U2501.1, U2501.2
unnamed: R2504.1, R2505.2, R2506.1, U2501.13
unnamed: R2509.1, R2510.2, R2514.1, U2501.10
unnamed: R2509.2, R2510.1, U2501.6, U2501.7
unnamed: R2511.1, R2512.2, R2513.1, U2501.9
unnamed: R2705.2, U2701.1
unnamed: R2706.2, U2701.3
unnamed: R2707.2, U2701.5
unnamed: R2708.2, U2701.7
unnamed: R2709.1, U2701.16
unnamed: R2710.1, U2701.14
unnamed: R2711.1, U2701.12
unnamed: R2712.1, U2701.10
unnamed: R2805.2, U2801.1
unnamed: R2806.2, U2801.3
unnamed: R2807.2, U2801.5
unnamed: R2808.2, U2801.7
unnamed: R2809.1, U2801.16
unnamed: R2810.1, U2801.14
unnamed: R2811.1, U2801.12
unnamed: R2812.1, U2801.10
unnamed: R2905.2, U2901.1
unnamed: R2906.2, U2901.3
unnamed: R2907.2, U2901.5
unnamed: R2908.2, U2901.7
unnamed: R2909.1, U2901.16
unnamed: R2910.1, U2901.14
unnamed: R2911.1, U2901.12
unnamed: R2912.1, U2901.10
unnamed: R3005.2, U3001.1
unnamed: R3006.2, U3001.3
unnamed: R3007.2, U3001.5
unnamed: R3008.2, U3001.7
unnamed: R3009.1, U3001.16
unnamed: R3010.1, U3001.14
unnamed: R3011.1, U3001.12
unnamed: R3012.1, U3001.10
unnamed: R3105.2, U3101.1
unnamed: R3106.2, U3101.3
unnamed: R3107.2, U3101.5
unnamed: R3108.2, U3101.7
unnamed: R3109.1, U3101.16
unnamed: R3110.1, U3101.14
unnamed: R3111.1, U3101.12
unnamed: R3112.1, U3101.10
unnamed: R3201.1, R3204.1, U3201.9
unnamed: R3201.2, U3201.1, U3201.2
unnamed: R3202.1, R3203.2, U3201.10
unnamed: U107.9, U108.14
unnamed: U108.9, U109.14
unnamed: U501.1, U503.1, U503.3
unnamed: U502.1, U503.5, U503.7
unnamed: U503.2, U503.4
unnamed: U503.6, U503.8
unnamed: U601.1, U603.1, U603.3
unnamed: U602.1, U603.5, U603.7
unnamed: U603.2, U603.4
unnamed: U603.6, U603.8
unnamed: U701.1, U703.1, U703.3
unnamed: U702.1, U703.5, U703.7
unnamed: U703.2, U703.4
unnamed: U703.6, U703.8
unnamed: U801.1, U803.1, U803.3
unnamed: U802.1, U803.5, U803.7
unnamed: U803.2, U803.4
unnamed: U803.6, U803.8
unnamed: U901.1, U903.1, U903.3
unnamed: U902.1, U903.5, U903.7
unnamed: U903.2, U903.4
unnamed: U903.6, U903.8
unnamed: U1001.1, U1003.1, U1003.3
unnamed: U1002.1, U1003.5, U1003.7
unnamed: U1003.2, U1003.4
unnamed: U1003.6, U1003.8
unnamed: U1101.1, U1103.1, U1103.3
unnamed: U1102.1, U1103.5, U1103.7
unnamed: U1103.2, U1103.4
unnamed: U1103.6, U1103.8
unnamed: U1201.1, U1203.1, U1203.3
unnamed: U1202.1, U1203.5, U1203.7
unnamed: U1203.2, U1203.4
unnamed: U1203.6, U1203.8
unnamed: U1301.1, U1303.1, U1303.3
unnamed: U1302.1, U1303.5, U1303.7
unnamed: U1303.2, U1303.4
unnamed: U1303.6, U1303.8
unnamed: U1401.1, U1403.1, U1403.3
unnamed: U1402.1, U1403.5, U1403.7
unnamed: U1403.2, U1403.4
unnamed: U1403.6, U1403.8
